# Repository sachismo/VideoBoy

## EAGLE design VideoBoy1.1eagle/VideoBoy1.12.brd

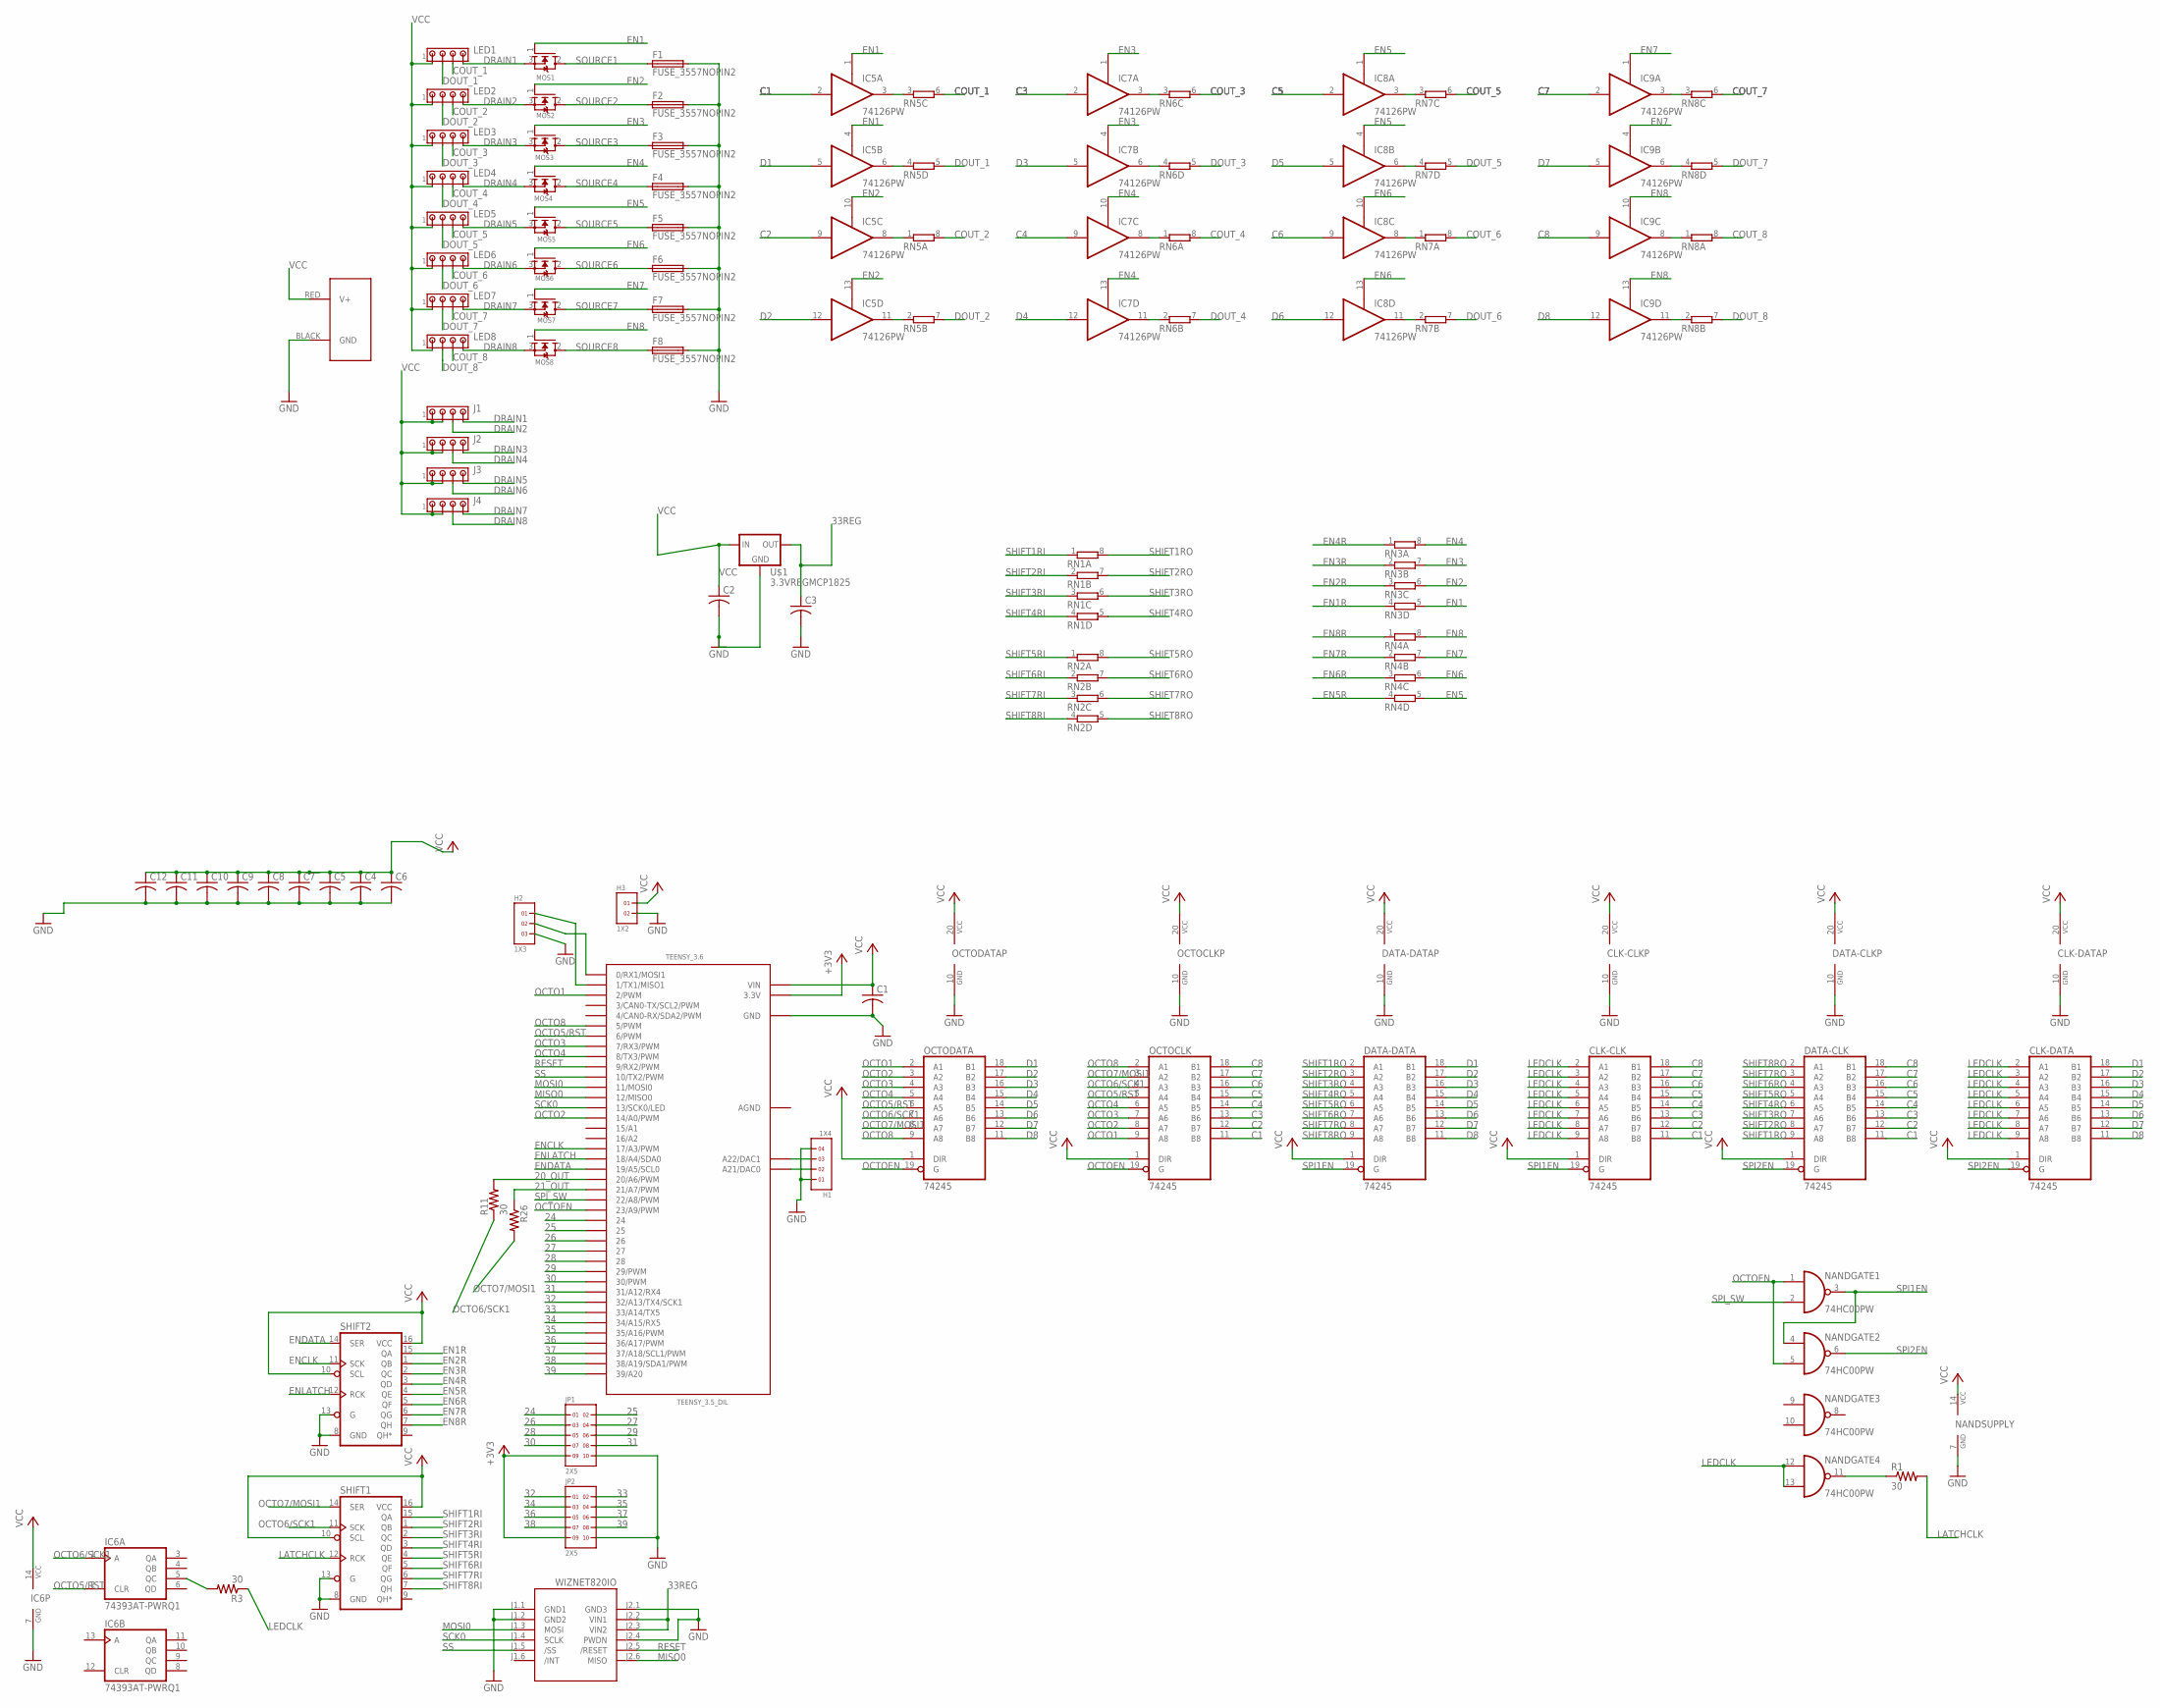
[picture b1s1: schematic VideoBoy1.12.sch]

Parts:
C1, C2, C3, C4, C5, C6, C7, C8, C9, C10, C11, C12: C-USC0603K; C0603K
CLK-CLK: 74245; TSSOP20
CLK-DATA: 74245; TSSOP20
DATA-CLK: 74245; TSSOP20
DATA-DATA: 74245; TSSOP20
F1, F2, F3, F4, F5, F6, F7, F8: FUSE_3557NOPIN2; 3557
H1: 1X4
H2: 1X3
H3: 1X2
IC5, IC7, IC8, IC9: 74126PW; TSSOP14
IC6: 74393AT-PWRQ1; TSSOP14
J1, J2, J3, J4: 4PIN-JST/TE; BOARDMOUNT-LED
J5: POWERPOLE_POWER25A; POWERPOLE_PAIR_25A
JP1, JP2: 2X5
LED1, LED2, LED3, LED4, LED5, LED6, LED7, LED8: 4PIN-JST/TE; BOARDMOUNT-LED
MOS1, MOS2, MOS3, MOS4, MOS5, MOS6, MOS7, MOS8: N-CHANNEL_MOSFET_TO-252; TO-252
NAND: 74HC00PW; TSSOP14
OCTOCLK: 74245; TSSOP20
OCTODATA: 74245; TSSOP20
R1, R3, R11: 30; R0603
R26: R-US_R0603; R0603
RN1, RN2, RN3, RN4, RN5, RN6, RN7, RN8: 4R-N0603-ARV; 0603-ARV
SHIFT1, SHIFT2: 74595PWR; TSSOP16
TEENSY_3.6: TEENSY_3.5_DIL
U$1: 3.3VREGMCP1825; SOT223
WIZNET820IO: WIZ820IO_DEVICE'DUAL-IN-LINE'; WIZ820IO

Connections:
20_OUT: R11.2, TEENSY_3.6.20/A6 (20/A6/PWM)
21_OUT: R26.1, TEENSY_3.6.21/A7 (21/A7/PWM)
24: JP1.1, TEENSY_3.6.24
25: JP1.2, TEENSY_3.6.25
26: JP1.3, TEENSY_3.6.26
27: JP1.4, TEENSY_3.6.27
28: JP1.5, TEENSY_3.6.28
29: JP1.6, TEENSY_3.6.29 (29/PWM)
30: JP1.7, TEENSY_3.6.30 (30/PWM)
31: JP1.8, TEENSY_3.6.31/A12 (31/A12/RX4)
32: JP2.1, TEENSY_3.6.32/A13 (32/A13/TX4/SCK1)
33: JP2.2, TEENSY_3.6.33/A14 (33/A14/TX5)
33REG: C3.1, U$1.3 (OUT), WIZNET820IO.J2.2 (VIN1), WIZNET820IO.J2.3 (VIN2)
34: JP2.3, TEENSY_3.6.34/A15 (34/A15/RX5)
35: JP2.4, TEENSY_3.6.35/A16 (35/A16/PWM)
36: JP2.5, TEENSY_3.6.36/A17 (36/A17/PWM)
37: JP2.6, TEENSY_3.6.37/A18 (37/A18/SCL1/PWM)
38: JP2.7, TEENSY_3.6.38/A19 (38/A19/SDA1/PWM)
39: JP2.8, TEENSY_3.6.39/A20
+3V3: JP1.9, JP2.9, TEENSY_3.6.3.3V, TEENSY_3.6.3.3V3 (3.3V)
AGND: TEENSY_3.6.AGND
C1: CLK-CLK.11 (B8), DATA-CLK.11 (B8), IC5.2 (I), OCTOCLK.11 (B8)
C2: CLK-CLK.12 (B7), DATA-CLK.12 (B7), IC5.9 (I), OCTOCLK.12 (B7)
C3: CLK-CLK.13 (B6), DATA-CLK.13 (B6), IC7.2 (I), OCTOCLK.13 (B6)
C4: CLK-CLK.14 (B5), DATA-CLK.14 (B5), IC7.9 (I), OCTOCLK.14 (B5)
C5: CLK-CLK.15 (B4), DATA-CLK.15 (B4), IC8.2 (I), OCTOCLK.15 (B4)
C6: CLK-CLK.16 (B3), DATA-CLK.16 (B3), IC8.9 (I), OCTOCLK.16 (B3)
C7: CLK-CLK.17 (B2), DATA-CLK.17 (B2), IC9.2 (I), OCTOCLK.17 (B2)
C8: CLK-CLK.18 (B1), DATA-CLK.18 (B1), IC9.9 (I), OCTOCLK.18 (B1)
COUT_1: LED1.3, RN5.6 (2)
COUT_2: LED2.3, RN5.8 (2)
COUT_3: LED3.3, RN6.6 (2)
COUT_4: LED4.3, RN6.8 (2)
COUT_5: LED5.3, RN7.6 (2)
COUT_6: LED6.3, RN7.8 (2)
COUT_7: LED7.3, RN8.6 (2)
COUT_8: LED8.3, RN8.8 (2)
CROUT9: IC5.3 (O), RN5.3 (1)
CROUT10: IC5.8 (O), RN5.1
CROUT11: IC7.3 (O), RN6.3 (1)
CROUT12: IC7.8 (O), RN6.1
CROUT13: IC9.3 (O), RN8.3 (1)
CROUT14: IC8.8 (O), RN7.1
CROUT15: IC9.8 (O), RN8.1
CROUT16: IC8.3 (O), RN7.3 (1)
D1: CLK-DATA.18 (B1), DATA-DATA.18 (B1), IC5.5 (I), OCTODATA.18 (B1)
D2: CLK-DATA.17 (B2), DATA-DATA.17 (B2), IC5.12 (I), OCTODATA.17 (B2)
D3: CLK-DATA.16 (B3), DATA-DATA.16 (B3), IC7.5 (I), OCTODATA.16 (B3)
D4: CLK-DATA.15 (B4), DATA-DATA.15 (B4), IC7.12 (I), OCTODATA.15 (B4)
D5: CLK-DATA.14 (B5), DATA-DATA.14 (B5), IC8.5 (I), OCTODATA.14 (B5)
D6: CLK-DATA.13 (B6), DATA-DATA.13 (B6), IC8.12 (I), OCTODATA.13 (B6)
D7: CLK-DATA.12 (B7), DATA-DATA.12 (B7), IC9.5 (I), OCTODATA.12 (B7)
D8: CLK-DATA.11 (B8), DATA-DATA.11 (B8), IC9.12 (I), OCTODATA.11 (B8)
DAC0: H1.2, TEENSY_3.6.A21 (A21/DAC0)
DAC1: H1.3, TEENSY_3.6.A22 (A22/DAC1)
DOUT_1: LED1.2, RN5.5 (2)
DOUT_2: LED2.2, RN5.7 (2)
DOUT_3: LED3.2, RN6.5 (2)
DOUT_4: LED4.2, RN6.7 (2)
DOUT_5: LED5.2, RN7.5 (2)
DOUT_6: LED6.2, RN7.7 (2)
DOUT_7: LED7.2, RN8.5 (2)
DOUT_8: LED8.2, RN8.7 (2)
DRAIN1: J1.4, LED1.4, MOS1.3 (S)
DRAIN2: J1.3, LED2.4, MOS2.3 (S)
DRAIN3: J2.4, LED3.4, MOS3.3 (S)
DRAIN4: J2.3, LED4.4, MOS4.3 (S)
DRAIN5: J3.4, LED5.4, MOS5.3 (S)
DRAIN6: J3.3, LED6.4, MOS6.3 (S)
DRAIN7: J4.4, LED7.4, MOS7.3 (S)
DRAIN8: J4.3, LED8.4, MOS8.3 (S)
DROUT9: IC5.6 (O), RN5.4 (1)
DROUT10: IC5.11 (O), RN5.2 (1)
DROUT11: IC7.6 (O), RN6.4 (1)
DROUT12: IC7.11 (O), RN6.2 (1)
DROUT13: IC9.6 (O), RN8.4 (1)
DROUT14: IC8.11 (O), RN7.2 (1)
DROUT15: IC9.11 (O), RN8.2 (1)
DROUT16: IC8.6 (O), RN7.4 (1)
EN1: IC5.1 (OE), IC5.4 (OE), MOS1.1 (G), RN3.5 (2)
EN1R: RN3.4 (1), SHIFT2.15 (QA)
EN2: IC5.10 (OE), IC5.13 (OE), MOS2.1 (G), RN3.6 (2)
EN2R: RN3.3 (1), SHIFT2.1 (QB)
EN3: IC7.1 (OE), IC7.4 (OE), MOS3.1 (G), RN3.7 (2)
EN3R: RN3.2 (1), SHIFT2.2 (QC)
EN4: IC7.10 (OE), IC7.13 (OE), MOS4.1 (G), RN3.8 (2)
EN4R: RN3.1, SHIFT2.3 (QD)
EN5: IC8.1 (OE), IC8.4 (OE), MOS5.1 (G), RN4.5 (2)
EN5R: RN4.4 (1), SHIFT2.4 (QE)
EN6: IC8.10 (OE), IC8.13 (OE), MOS6.1 (G), RN4.6 (2)
EN6R: RN4.3 (1), SHIFT2.5 (QF)
EN7: IC9.1 (OE), IC9.4 (OE), MOS7.1 (G), RN4.7 (2)
EN7R: RN4.2 (1), SHIFT2.6 (QG)
EN8: IC9.10 (OE), IC9.13 (OE), MOS8.1 (G), RN4.8 (2)
EN8R: RN4.1, SHIFT2.7 (QH)
ENCLK: SHIFT2.11 (SCK), TEENSY_3.6.17/A3 (17/A3/PWM)
ENDATA: SHIFT2.14 (SER), TEENSY_3.6.19/A5 (19/A5/SCL0)
ENLATCH: SHIFT2.12 (RCK), TEENSY_3.6.18/A4 (18/A4/SDA0)
GND: C1.2, C2.2, C3.2, C4.2, C5.2, C6.2, C7.2, C8.2, C9.2, C10.2, C11.2, C12.2, CLK-CLK.10 (GND), CLK-DATA.10 (GND), DATA-CLK.10 (GND), DATA-DATA.10 (GND), F1.3 (2), F1.4 (2), F2.3 (2), F2.4 (2), F3.3 (2), F3.4 (2), F4.3 (2), F4.4 (2), F5.3 (2), F5.4 (2), F6.3 (2), F6.4 (2), F7.3 (2), F7.4 (2), F8.3 (2), F8.4 (2), H1.1, H1.4, H2.3, H3.2, IC5.7 (GND), IC6.7 (GND), IC7.7 (GND), IC8.7 (GND), IC9.7 (GND), J5.BLACK (GND), JP1.10, JP2.10, NAND.7 (GND), OCTOCLK.10 (GND), OCTODATA.10 (GND), SHIFT1.8 (GND), SHIFT1.13 (G), SHIFT2.8 (GND), SHIFT2.13 (G), TEENSY_3.6.GND, TEENSY_3.6.GND1 (GND), U$1.2 (GND), U$1.4 (GND), WIZNET820IO.J1.1 (GND1), WIZNET820IO.J1.2 (GND2), WIZNET820IO.J2.1 (GND3), WIZNET820IO.J2.4 (PWDN)
LATCHCLK: R1.2, SHIFT1.12 (RCK)
LATCHCLKR: NAND.11 (O), R1.1
LEDCLK: CLK-CLK.2 (A1), CLK-CLK.3 (A2), CLK-CLK.4 (A3), CLK-CLK.5 (A4), CLK-CLK.6 (A5), CLK-CLK.7 (A6), CLK-CLK.8 (A7), CLK-CLK.9 (A8), CLK-DATA.2 (A1), CLK-DATA.3 (A2), CLK-DATA.4 (A3), CLK-DATA.5 (A4), CLK-DATA.6 (A5), CLK-DATA.7 (A6), CLK-DATA.8 (A7), CLK-DATA.9 (A8), NAND.12 (I0), NAND.13 (I1), R3.1
LEDCLKR: IC6.5 (QC), R3.2
MISO0: TEENSY_3.6.12 (12/MISO0), WIZNET820IO.J2.6 (MISO)
MOSI0: TEENSY_3.6.11 (11/MOSI0), WIZNET820IO.J1.3 (MOSI)
unnamed: H2.2, TEENSY_3.6.0 (0/RX1/MOSI1)
unnamed: H2.1, TEENSY_3.6.1 (1/TX1/MISO1)
OCTO1: OCTOCLK.9 (A8), OCTODATA.2 (A1), TEENSY_3.6.2 (2/PWM)
OCTO2: OCTOCLK.8 (A7), OCTODATA.3 (A2), TEENSY_3.6.14/A0 (14/A0/PWM)
OCTO3: OCTOCLK.7 (A6), OCTODATA.4 (A3), TEENSY_3.6.7 (7/RX3/PWM)
OCTO4: OCTOCLK.6 (A5), OCTODATA.5 (A4), TEENSY_3.6.8 (8/TX3/PWM)
OCTO5/RST: IC6.2 (CLR), OCTOCLK.5 (A4), OCTODATA.6 (A5), TEENSY_3.6.6 (6/PWM)
OCTO6/SCK1: IC6.1 (A), OCTOCLK.4 (A3), OCTODATA.7 (A6), R11.1, SHIFT1.11 (SCK)
OCTO7/MOSI1: OCTOCLK.3 (A2), OCTODATA.8 (A7), R26.2, SHIFT1.14 (SER)
OCTO8: OCTOCLK.2 (A1), OCTODATA.9 (A8), TEENSY_3.6.5 (5/PWM)
OCTOEN: NAND.1 (I0), NAND.5 (I1), OCTOCLK.19 (G), OCTODATA.19 (G), TEENSY_3.6.23/A9 (23/A9/PWM)
RESET: TEENSY_3.6.9 (9/RX2/PWM), WIZNET820IO.J2.5 (/RESET)
SCK0: TEENSY_3.6.13 (13/SCK0/LED), WIZNET820IO.J1.4 (SCLK)
SHIFT1RI: RN1.1, SHIFT1.15 (QA)
SHIFT1RO: DATA-CLK.9 (A8), DATA-DATA.2 (A1), RN1.8 (2)
SHIFT2RI: RN1.2 (1), SHIFT1.1 (QB)
SHIFT2RO: DATA-CLK.8 (A7), DATA-DATA.3 (A2), RN1.7 (2)
SHIFT3RI: RN1.3 (1), SHIFT1.2 (QC)
SHIFT3RO: DATA-CLK.7 (A6), DATA-DATA.4 (A3), RN1.6 (2)
SHIFT4RI: RN1.4 (1), SHIFT1.3 (QD)
SHIFT4RO: DATA-CLK.6 (A5), DATA-DATA.5 (A4), RN1.5 (2)
SHIFT5RI: RN2.1, SHIFT1.4 (QE)
SHIFT5RO: DATA-CLK.5 (A4), DATA-DATA.6 (A5), RN2.8 (2)
SHIFT6RI: RN2.2 (1), SHIFT1.5 (QF)
SHIFT6RO: DATA-CLK.4 (A3), DATA-DATA.7 (A6), RN2.7 (2)
SHIFT7RI: RN2.3 (1), SHIFT1.6 (QG)
SHIFT7RO: DATA-CLK.3 (A2), DATA-DATA.8 (A7), RN2.6 (2)
SHIFT8RI: RN2.4 (1), SHIFT1.7 (QH)
SHIFT8RO: DATA-CLK.2 (A1), DATA-DATA.9 (A8), RN2.5 (2)
SOURCE1: F1.1, MOS1.2 (D)
SOURCE2: F2.1, MOS2.2 (D)
SOURCE3: F3.1, MOS3.2 (D)
SOURCE4: F4.1, MOS4.2 (D)
SOURCE5: F5.1, MOS5.2 (D)
SOURCE6: F6.1, MOS6.2 (D)
SOURCE7: F7.1, MOS7.2 (D)
SOURCE8: F8.1, MOS8.2 (D)
SPI1EN: CLK-CLK.19 (G), DATA-DATA.19 (G), NAND.3 (O), NAND.4 (I0)
SPI2EN: CLK-DATA.19 (G), DATA-CLK.19 (G), NAND.6 (O)
SPI_SW: NAND.2 (I1), TEENSY_3.6.22/A8 (22/A8/PWM)
SS: TEENSY_3.6.10 (10/TX2/PWM), WIZNET820IO.J1.5 (/SS)
VCC: C1.1, C2.1, C4.1, C5.1, C6.1, C7.1, C8.1, C9.1, C10.1, C11.1, C12.1, CLK-CLK.1 (DIR), CLK-CLK.20 (VCC), CLK-DATA.1 (DIR), CLK-DATA.20 (VCC), DATA-CLK.1 (DIR), DATA-CLK.20 (VCC), DATA-DATA.1 (DIR), DATA-DATA.20 (VCC), H3.1, IC5.14 (VCC), IC6.14 (VCC), IC7.14 (VCC), IC8.14 (VCC), IC9.14 (VCC), J1.1, J1.2, J2.1, J2.2, J3.1, J3.2, J4.1, J4.2, J5.RED (V+), LED1.1, LED2.1, LED3.1, LED4.1, LED5.1, LED6.1, LED7.1, LED8.1, NAND.14 (VCC), OCTOCLK.1 (DIR), OCTOCLK.20 (VCC), OCTODATA.1 (DIR), OCTODATA.20 (VCC), SHIFT1.10 (SCL), SHIFT1.16 (VCC), SHIFT2.10 (SCL), SHIFT2.16 (VCC), TEENSY_3.6.VIN, U$1.1 (IN)

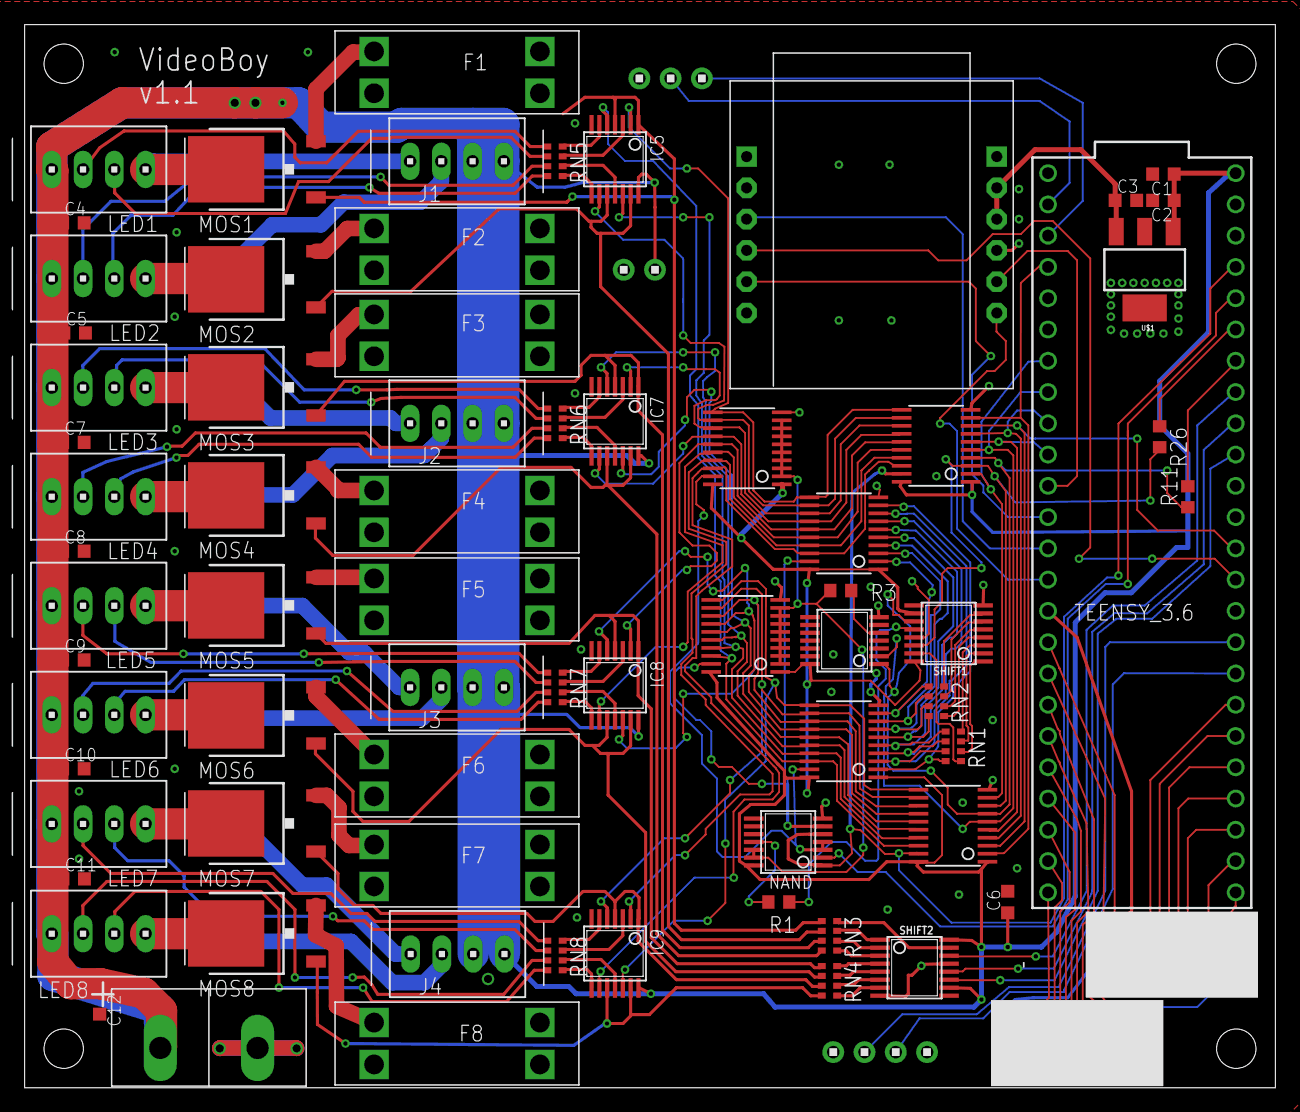
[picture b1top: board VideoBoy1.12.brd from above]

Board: 2 copper layers, 101.6 x 86.4 mm, 75 parts (0 on the bottom side), 146 nets.

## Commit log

2017-08-29 Added circuit board files
2017-08-30 edited circuit drains
